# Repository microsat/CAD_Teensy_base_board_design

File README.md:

# Teensy_base_board_design
The design files for base controller

plan is for a pcb...

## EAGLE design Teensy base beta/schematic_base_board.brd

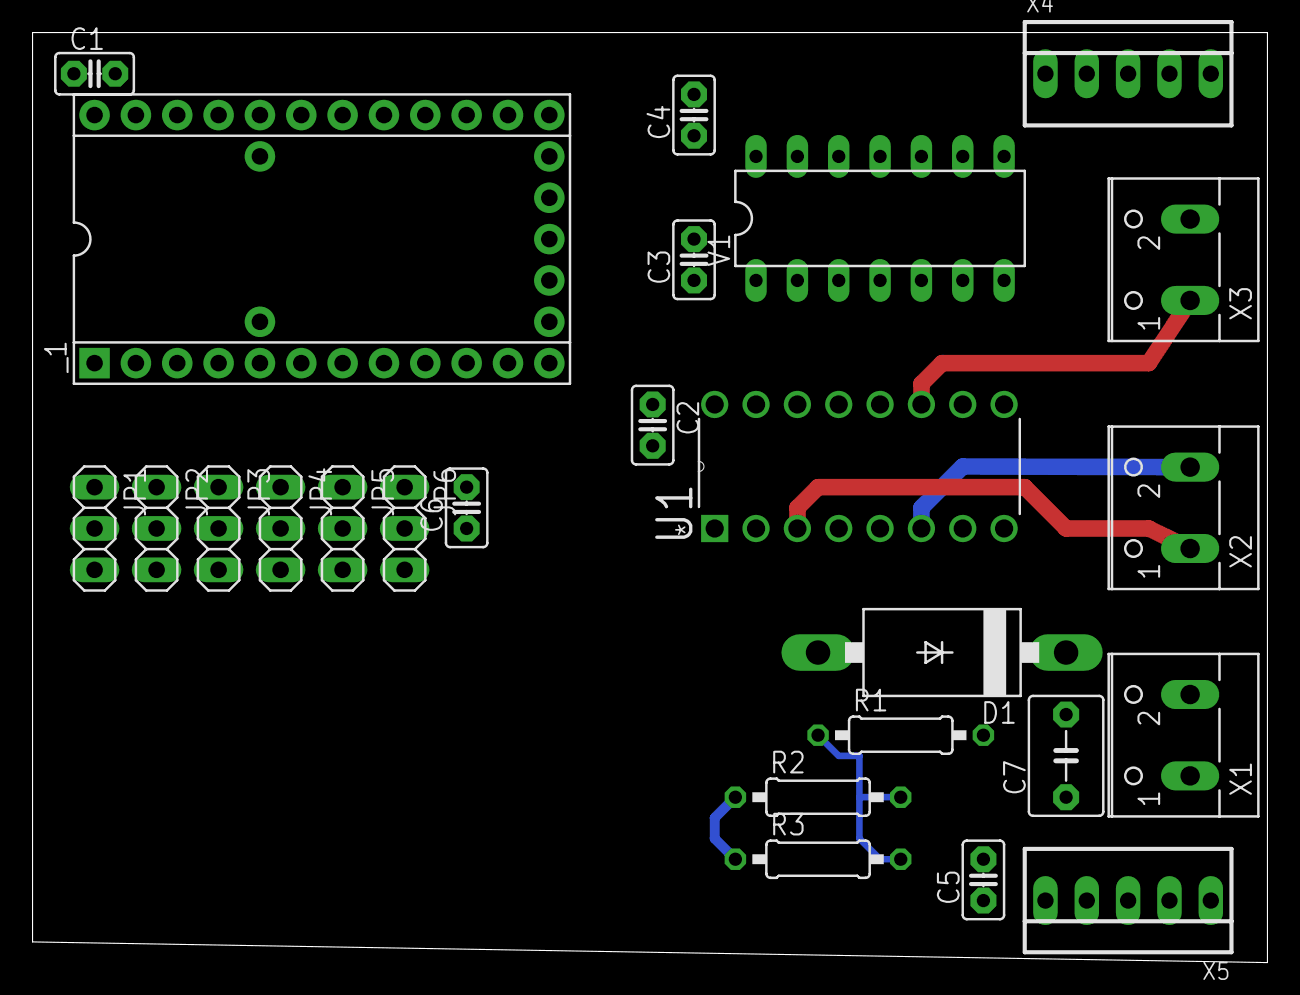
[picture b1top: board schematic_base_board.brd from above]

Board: 2 copper layers, 75.9 x 57.1 mm, 25 parts (0 on the bottom side), 13 nets.

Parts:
C1, C2, C3, C4, C5, C6: C2.5-2
C7: C5B4.5
D1: C2673
JP1, JP2, JP3, JP4, JP5, JP6: 1X03
R1, R2, R3: 0207/10
U1: SN754410NE; DIP254P762X508-16
V1: 7486N; DIL14
X1, X2, X3: W237-102
X4, X5: 22-23-2051
_1: TEENSY

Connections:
ADC_VMOTOR: R1.1, R2.2, R3.2, _1.F0
CHA_ENC_L: V1.1, X5.5
CHA_ENC_R: V1.4, X4.5
CHB_ENC_L: V1.2, X5.4
CHB_ENC_R: V1.5, X4.4
GND: C1.2, C2.2, C3.2, C4.2, C5.2, C6.2, C7.2, JP1.1, JP2.1, JP3.1, JP4.1, JP5.1, JP6.1, R2.1, R3.1, U1.5, U1.12, U1.13, V1.9, V1.10, V1.12, V1.13, X1.2, X4.1, X5.1, _1.GND, _1.GRND1
unnamed: D1.C, U1.8
unnamed: U1.3, X2.1
unnamed: U1.6, X2.2
unnamed: U1.11, X3.1
unnamed: U1.14, X3.2
VCC: C1.1, C2.1, C3.1, C4.1, C5.1, C6.1, JP1.2, JP2.2, JP3.2, JP4.2, JP5.2, JP6.2, U1.16, X4.3, X5.3, _1.5V2, _1.+5V
VMOTOR: C7.1, D1.A, R1.2, X1.1

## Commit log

2015-05-07 :octocat: Added .gitattributes & .gitignore files
2015-05-07 added data sheets
2015-05-07 added readme
2015-05-07 start of drawing
2015-05-08 working on design
2015-05-10 removing not need files
2015-05-10 not needed
2015-05-11 clean up

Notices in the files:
parts and their libraries:
teensy: Licensed Under Creative Commons
